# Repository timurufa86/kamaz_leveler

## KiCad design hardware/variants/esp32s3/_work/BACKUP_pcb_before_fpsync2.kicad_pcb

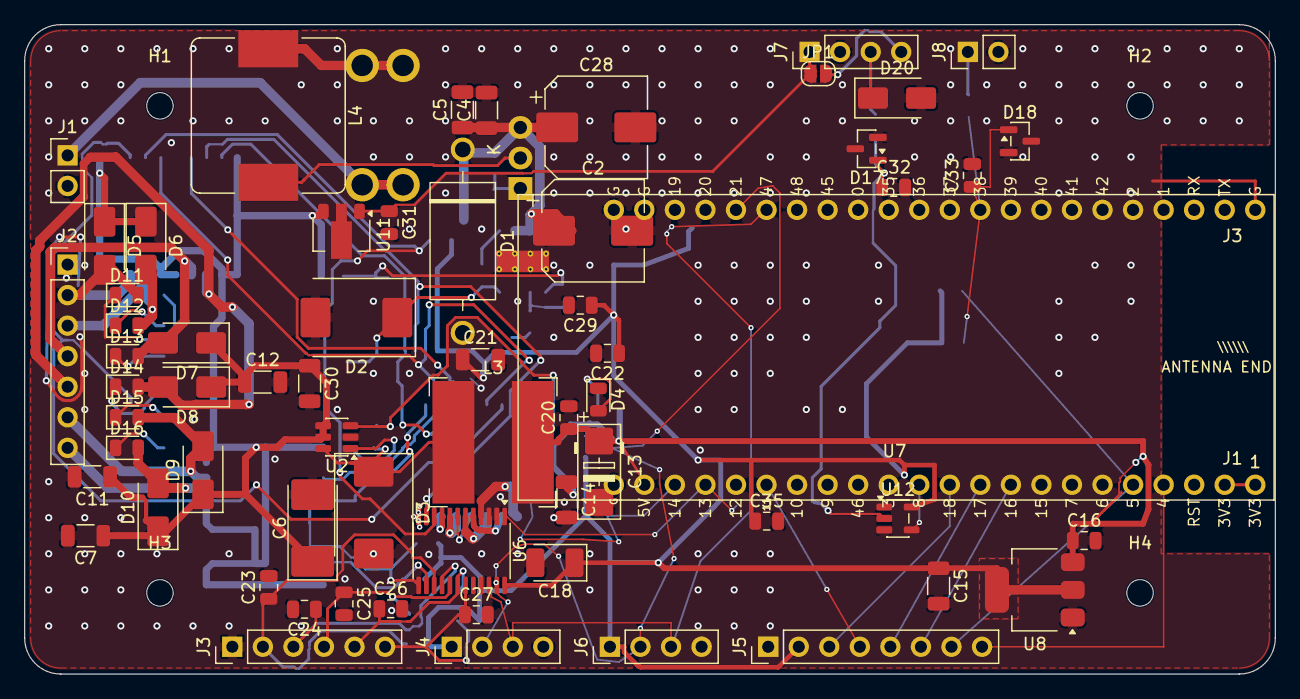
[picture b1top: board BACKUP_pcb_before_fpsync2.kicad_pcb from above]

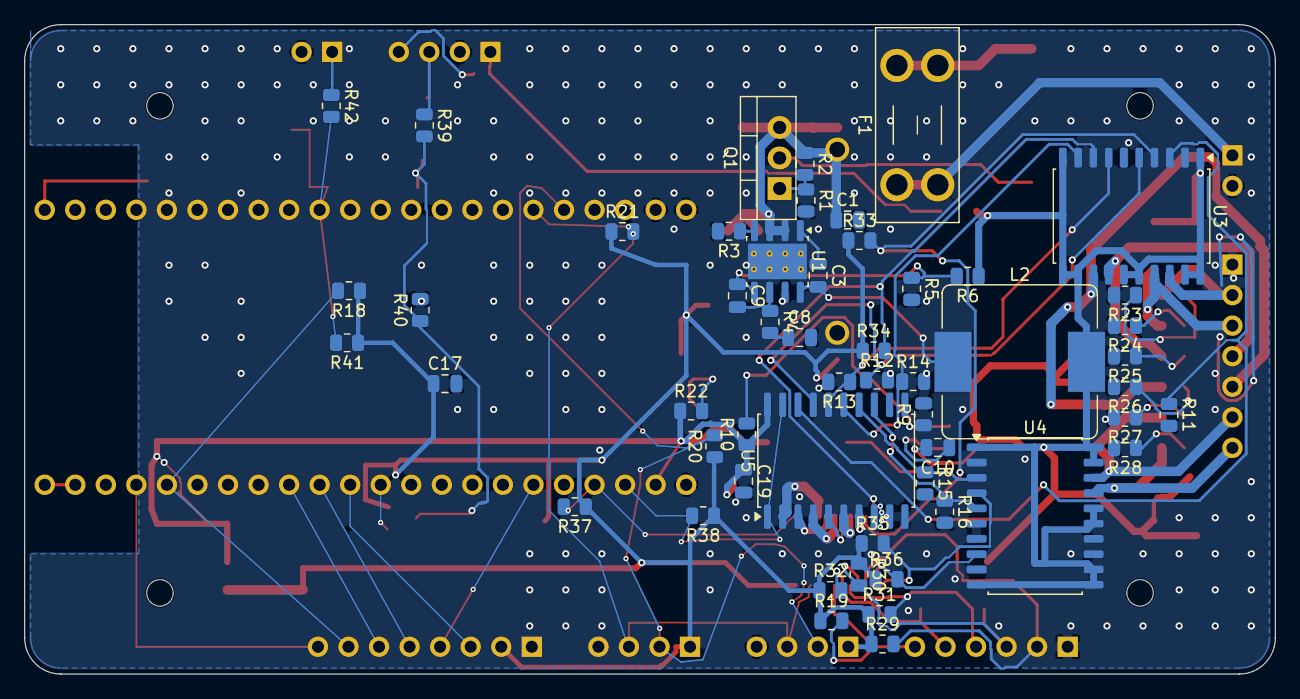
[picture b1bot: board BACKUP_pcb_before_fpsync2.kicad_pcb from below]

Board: 2 copper layers, 104.0 x 54.0 mm, 120 parts (53 on the bottom side), 70 nets.

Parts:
C1, C3, C10, C16, C17, C20, C22, C23, C24, C25, C26, C27, C29, C31, C32, C33, C35: 100nF; C_0805_2012Metric
C2: 470uF; CP_Elec_8x10
C4, C5, C7, C11, C12, C14, C15, C21, C30: 10uF; C_1206_3216Metric
C6: 100uF; CP_EIA-7132-20_AVX-U
C8: 4.7nF; C_0805_2012Metric
C9: 47pF; C_0805_2012Metric
C13: 100uF; CP_EIA-6032-15_Kemet-U_Pad2.25x2.35mm_HandSolder
C18: 10uF; CP_EIA-3528-12_Kemet-T_HandSolder
C19: 10uF; C_0805_2012Metric
C28: 330uF/35V; CP_Elec_8x10
D1: 1.5KE36CA; D_DO-201AD_P15.24mm_Horizontal_Pad2.0_Drill1.3
D2: SS54; D_SMC
D3: SS34; D_SMC
D4, D11, D12, D13, D14, D15, D16: LED; LED_0805_2012Metric
D5, D6, D7, D8, D9, D10: SS34; D_SMA
D17, D18: BZX84C3V3; SOT-23
D20: SMAJ12A; D_SMA
F1: 5A; Fuseholder_Blade_Mini_Keystone_3568
H1, H2, H3, H4: MountingHole; MountingHole_3.2mm_M3_Pad6
J1, J8: Conn_01x02_Pin; PinHeader_1x02_P2.54mm_Vertical
J2: Conn_01x07_Pin; PinHeader_1x07_P2.54mm_Vertical
J3: Conn_01x06_Pin; PinHeader_1x06_P2.54mm_Vertical
J4, J6, J7: Conn_01x04_Pin; PinHeader_1x04_P2.54mm_Vertical
J5: Conn_01x08_Pin; PinHeader_1x08_P2.54mm_Vertical
JP1: Jumper; SolderJumper-2_P1.3mm_Open_RoundedPad1.0x1.5mm
L2: 33uH; L_Bourns_SRP1245A
L3: 10uH; L_Bourns-SRN1060
L4: 10uH; L_Bourns_SRP1245A
Q1: IRF9540N; TO-220-3_Vertical
R1, R4, R9, R11, R12, R13, R14, R15, R16, R18, R19, R29, R30, R31, R32, R33, R34, R35, R36, R37, R38, R39, R42: 10k; R_0805_2012Metric
R2: 47k; R_0805_2012Metric
R3, R41: 100k; R_0805_2012Metric
R5: 6.49k; R_0805_2012Metric
R6: 91k; R_0805_2012Metric
R10: 52.3k; R_0805_2012Metric
R20, R21, R23, R24, R25, R26, R27, R28: 4.7k; R_0805_2012Metric
R22: 1k; R_0805_2012Metric
R40: 20k; R_0805_2012Metric
U1: TPS54560BDDA; SOIC-8-1EP_3.9x4.9mm_P1.27mm_EP2.95x4.9mm_Mask2.71x3.4mm_Th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
U2: AP3211K; SOT-23-6
U3, U4: BTS724G; Infineon_SOIC-20W_7.6x12.8mm_P1.27mm
U5: 74HCT541; SOIC-20W_7.5x12.8mm_P1.27mm
U6: PCAL9555APW; TSSOP-24_4.4x7.8mm_P0.65mm
U7: ESP32-S3-DevKitC-1_N16R8; ESP32-S3-DevKitC-1_Socket_2x22_P2.54mm
U8: AMS1117-3.3; SOT-223-3_TabPin2
U11: 78L08; SOT-89-3
U12: 74LVC1G14; SOT-23-5

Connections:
+3V3: C15.1, C17.1, C18.1, C21.1, C22.1, C29.1, C35.1, J4.1, J5.2, J6.1, R18.1, R19.1, R20.1, R21.1, R29.1, R30.1, R31.1, R32.1, R33.1, R34.1, R35.1, R36.1, R37.1, R38.1, R41.1, U6.24 (VDD), U8.2, U12.5 (VCC)
+3V3_ESP: U7.1, U7.2
+5V: C13.1, C14.1, C16.1, C19.1, C20.1, L3.2, R10.1, R22.1, U5.20 (VCC), U7.21, U8.3
+12V: C6.1, C7.1, C11.1, C12.1, C30.1, D5.1 (K), D6.1 (K), D7.1 (K), D8.1 (K), D9.1 (K), D10.1 (K), L2.2, R6.1, U2.4 (EN), U2.5 (IN), U3.1 (VBB), U3.10 (VBB), U3.11 (VBB), U3.12 (VBB), U3.15 (VBB), U3.16 (VBB), U3.19 (VBB), U3.20 (VBB), U4.1 (VBB), U4.10 (VBB), U4.11 (VBB), U4.12 (VBB), U4.15 (VBB), U4.16 (VBB), U4.19 (VBB), U4.20 (VBB), U11.3 (IN)
+24V: C1.1, C2.1, C4.1, C5.1, C28.1, D1.1 (A1), Q1.3 (S), R2.1, U1.2 (VIN), U1.3 (EN)
/+8V_SENS: C31.1, J7.1, JP1.1 (A), U11.1 (OUT)
/+24V_IN: F1.1, J1.1
/BOOT1: C3.1, U1.1 (BOOT)
/BOOT2: C10.1, U2.1 (BS)
/BUT1: C23.1, J3.2, R29.2, U6.15 (IO1_2)
/BUT2: C24.1, J3.3, R30.2, U6.16 (IO1_3)
/BUT3: C25.1, J3.4, R31.2, U6.17 (IO1_4)
/BUT4: C26.1, J3.5, R32.2, U6.18 (IO1_5)
/BUT5: C27.1, J3.6, R19.2, U6.19 (IO1_6)
/COMP1: C9.2, R4.1, U1.6 (COMP)
/COMP1_R: C8.1, R4.2
/DISP_BL: J5.8, U7.4
/DISP_CS: J5.7, R18.2, U7.5
/DISP_DC: J5.6, U7.9
/DISP_MOSI: J5.4, U7.17
/DISP_RES: J5.5, U7.10
/DISP_SCLK: J5.3, U7.11
/EXT_8V: J7.4, JP1.2 (B)
/FB1: C9.1, R5.1, R6.2, U1.5 (FB)
/FB2: R9.1, R10.2, U2.3 (FB)
/I2C_SCL: J4.3, J6.3, R21.2, U6.22 (SCL), U7.39
/I2C_SDA: J4.2, J6.2, R20.2, U6.23 (SDA), U7.40
/INT_MCU: R37.2, U6.1 (~INT), U7.19
/LED_A: D4.2 (A), R22.2
/PRES_IN: J8.1, R42.1
/PRES_SW: C33.1, D18.1 (K), R41.2, R42.2, U7.32
/Q1_GATE: Q1.1 (G), R1.1, R2.2
/RT1: R3.1, U1.4 (RT/CLK)
/SPEED_PULSE: U7.12, U12.4
/SPEED_SIG: D20.1 (A1), J7.3, R39.1
/SP_DIV: C32.1, D17.1 (K), R39.2, R40.1, U12.2
/ST_U3_12: R33.2, U3.4 (ST1/2), U6.10 (IO0_6)
/ST_U3_34: R34.2, U3.8 (ST3/4), U6.11 (IO0_7)
/ST_U4_12: R35.2, U4.4 (ST1/2), U6.13 (IO1_0)
/ST_U4_34: R36.2, U4.8 (ST3/4), U6.14 (IO1_1)
/SW1: C3.2, D2.1 (K), L2.1, U1.8 (SW)
/SW2: C10.2, D3.1 (K), L3.1, U2.6 (SW)
/VALVE_BUB1: D5.2 (A), D11.2 (A), J2.2, U3.18 (OUT1)
/VALVE_BUB2: D6.2 (A), D12.2 (A), J2.3, U3.17 (OUT2)
/VALVE_BUB3: D7.2 (A), D13.2 (A), J2.4, U3.14 (OUT3)
/VALVE_BUB4: D8.2 (A), D14.2 (A), J2.5, U3.13 (OUT4)
/VALVE_DEFL: D10.2 (A), D16.2 (A), J2.7, U4.17 (OUT2)
/VALVE_INFL: D9.2 (A), D15.2 (A), J2.6, U4.18 (OUT1)
/VIN_FILT: L4.2, Q1.2 (D)
/VIN_FUSED: F1.2, L4.1
/VLV_DRV1: R11.1, U3.3 (IN1), U5.18 (Y0)
/VLV_DRV2: R12.1, U3.5 (IN2), U5.17 (Y1)
/VLV_DRV3: R13.1, U3.7 (IN3), U5.16 (Y2)
/VLV_DRV4: R14.1, U3.9 (IN4), U5.15 (Y3)
/VLV_DRV5: R15.1, U4.3 (IN1), U5.14 (Y4)
/VLV_DRV6: R16.1, U4.5 (IN2), U5.13 (Y5)
/VLV_EN: R38.2, U5.1 (G1), U5.19 (G2), U7.20
/VLV_IN1: U5.2 (A0), U6.4 (IO0_0)
/VLV_IN2: U5.3 (A1), U6.5 (IO0_1)
/VLV_IN3: U5.4 (A2), U6.6 (IO0_2)
/VLV_IN4: U5.5 (A3), U6.7 (IO0_3)
/VLV_IN5: U5.6 (A4), U6.8 (IO0_4)
/VLV_IN6: U5.7 (A5), U6.9 (IO0_5)
/VLV_LED1: D11.1 (K), R23.1
/VLV_LED2: D12.1 (K), R24.1
/VLV_LED3: D13.1 (K), R25.1
/VLV_LED4: D14.1 (K), R26.1
/VLV_LED5: D15.1 (K), R27.1
/VLV_LED6: D16.1 (K), R28.1
GND: C1.2, C2.2, C4.2, C5.2, C6.2, C7.2, C8.2, C11.2, C12.2, C13.2, C14.2, C15.2, C16.2, C17.2, C18.2, C19.2, C20.2, C21.2, C22.2, C23.2, C24.2, C25.2, C26.2, C27.2, C28.2, C29.2, C30.2, C31.2, C32.2, C33.2, C35.2, D1.2 (A2), D2.2 (A), D3.2 (A), D4.1 (K), D17.2 (A), D18.2 (A), D20.2 (A2), J1.2, J2.1, J3.1, J4.4, J5.1, J6.4, J7.2, J8.2, R1.2, R3.2, R5.2, R9.2, R11.2, R12.2, R13.2, R14.2, R15.2, R16.2, R23.2, R24.2, R25.2, R26.2, R27.2, R28.2, R40.2, U1.7 (GND), U1.9 (GND), U2.2 (GND), U3.2 (GND1/2), U3.6 (GND3/4), U4.2 (GND1/2), U4.6 (GND3/4), U4.7 (IN3), U4.9 (IN4), U5.8 (A6), U5.9 (A7), U5.10 (GND), U6.2 (A1), U6.3 (A2), U6.12 (VSS), U6.21 (A0), U7.22, U7.23, U7.43, U7.44, U8.1, U11.2 (GND), U12.3 (GND)

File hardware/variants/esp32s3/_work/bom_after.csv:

"Reference","Value","Footprint"
"C1,C3,C10,C16,C17,C20,C22-C27,C29,C31-C33,C35","100nF","Capacitor_SMD:C_0805_2012Metric"
"C2","470uF","Capacitor_SMD:CP_Elec_8x10"
"C4,C5,C7,C11,C12,C14,C15,C21,C30","10uF","Capacitor_SMD:C_1206_3216Metric"
"C6","100uF","Capacitor_Tantalum_SMD:CP_EIA-7132-20_AVX-U"
"C8","4.7nF","Capacitor_SMD:C_0805_2012Metric"
"C9","47pF","Capacitor_SMD:C_0805_2012Metric"
"C13","100uF","PCM_Capacitor_Tantalum_SMD_AKL:CP_EIA-6032-15_Kemet-U_Pad2.25x2.35mm_HandSolder"
"C18","10uF","Capacitor_Tantalum_SMD:CP_EIA-3528-12_Kemet-T_HandSolder"
"C19","10uF","Capacitor_SMD:C_0805_2012Metric"
"C28","330uF/35V","Capacitor_SMD:CP_Elec_8x10"
"D1","1.5KE36CA","kamaz_leveler:D_DO-201AD_P15.24mm_Horizontal_Pad2.0_Drill1.3"
"D2","SS54","Diode_SMD:D_SMC"
"D3","SS34","Diode_SMD:D_SMC"
"D4,D11-D16","LED","LED_SMD:LED_0805_2012Metric"
"D5-D10","SS34","Diode_SMD:D_SMA"
"D17,D18","BZX84C3V3","Package_TO_SOT_SMD:SOT-23"
"D20","SMAJ12A","Diode_SMD:D_SMA"
"F1","5A","Fuse:Fuseholder_Blade_Mini_Keystone_3568"
"J1,J8","Conn_01x02_Pin","Connector_PinHeader_2.54mm:PinHeader_1x02_P2.54mm_Vertical"
"J2","Conn_01x07_Pin","Connector_PinHeader_2.54mm:PinHeader_1x07_P2.54mm_Vertical"
"J3","Conn_01x06_Pin","Connector_PinHeader_2.54mm:PinHeader_1x06_P2.54mm_Vertical"
"J4,J6,J7","Conn_01x04_Pin","Connector_PinHeader_2.54mm:PinHeader_1x04_P2.54mm_Vertical"
"J5","Conn_01x08_Pin","Connector_PinHeader_2.54mm:PinHeader_1x08_P2.54mm_Vertical"
"JP1","Jumper","Jumper:SolderJumper-2_P1.3mm_Open_RoundedPad1.0x1.5mm"
"L2","33uH","Inductor_SMD:L_Bourns_SRP1245A"
"L3","10uH","Inductor_SMD:L_Bourns-SRN1060"
"L4","10uH","Inductor_SMD:L_Bourns_SRP1245A"
"Q1","IRF9540N","Package_TO_SOT_THT:TO-220-3_Vertical"
"R1,R4,R9,R11-R16,R18,R19,R29-R39,R42","10k","Resistor_SMD:R_0805_2012Metric"
"R2","47k","Resistor_SMD:R_0805_2012Metric"
"R3,R41","100k","Resistor_SMD:R_0805_2012Metric"
"R5","6.49k","Resistor_SMD:R_0805_2012Metric"
"R6","91k","Resistor_SMD:R_0805_2012Metric"
"R10","52.3k","Resistor_SMD:R_0805_2012Metric"
"R20,R21,R23-R28","4.7k","Resistor_SMD:R_0805_2012Metric"
"R22","1k","Resistor_SMD:R_0805_2012Metric"
"R40","20k","Resistor_SMD:R_0805_2012Metric"
"U1","TPS54560BDDA","Package_SO:SOIC-8-1EP_3.9x4.9mm_P1.27mm_EP2.95x4.9mm_Mask2.71x3.4mm_ThermalVias"
"U2","AP3211K","Package_TO_SOT_SMD:SOT-23-6"
"U3,U4","BTS724G","Package_SO:Infineon_SOIC-20W_7.6x12.8mm_P1.27mm"
"U5","74HCT541","Package_SO:SOIC-20W_7.5x12.8mm_P1.27mm"
"U6","PCAL9555APW","Package_SO:TSSOP-24_4.4x7.8mm_P0.65mm"
"U7","ESP32-S3-DevKitC-1_N16R8","kamaz_leveler:ESP32-S3-DevKitC-1_Socket_2x22_P2.54mm"
"U8","AMS1117-3.3","Package_TO_SOT_SMD:SOT-223-3_TabPin2"
"U11","78L08","Package_TO_SOT_SMD:SOT-89-3"
"U12","74LVC1G14","Package_TO_SOT_SMD:SOT-23-5"
